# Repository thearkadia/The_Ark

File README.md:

# The Ark - ¿Democracy's Favorite Device?

The Ark is a portable computer that can be upgraded, modded, or repaired by the user since it uses open-source software, the pcb files are available, and the parts can be purchased individually. It is powered by the [Raspberry Pi Compute Module](https://www.raspberrypi.org/products/compute-module-3-plus-lite/), and runs a modified version of Debian.

# Simplifying Democracy
One of the goals of the Ark is to simplify the process of participating in a democracy for citizens, journalists, and politicians in a safe and transparent way. To simplify participating in a Democracy we will develop open source applications that focus on different key aspects of a Democracy. 

(images below are only mockups of the applications. all companies, charities, and names are used for demonstration purposes only) 

* An open source application that allows citizens to keep track of the voting history of their representatives. 

# Simplifying Budgets, Boycotts, and Taxes

* An application for journalists and charities to easily recieve reccuring donations from supporters. 

* An application to simplify the process of boycotting companies by displaying what products and companies a conglomerate owns or has a stake in. With a search feature to find alternatives to the product\service they are looking to purchase. 

 <p align="center">
  <a href="mailto:nixoye@protonmail.com"></center>
Email Us</a> </p>

<p align="center"> <a href="https://www.crowdsupply.com/the-arkadia/the-ark-dev-kit"> Crowdsupply Campaign </center> </p></a>
<p>
 <p align="center">
  Follow us on <a href="https://instagram.com/thearkadia">Instagram </a> or <a href="http://www.twitter.com/nixoye">Twitter</a></p>
    
<p align="center">  It has to start somewhere. It has to start sometime.
      </center> 
 </p>

<p align="center"> What better place than here? What better time than now? </center>

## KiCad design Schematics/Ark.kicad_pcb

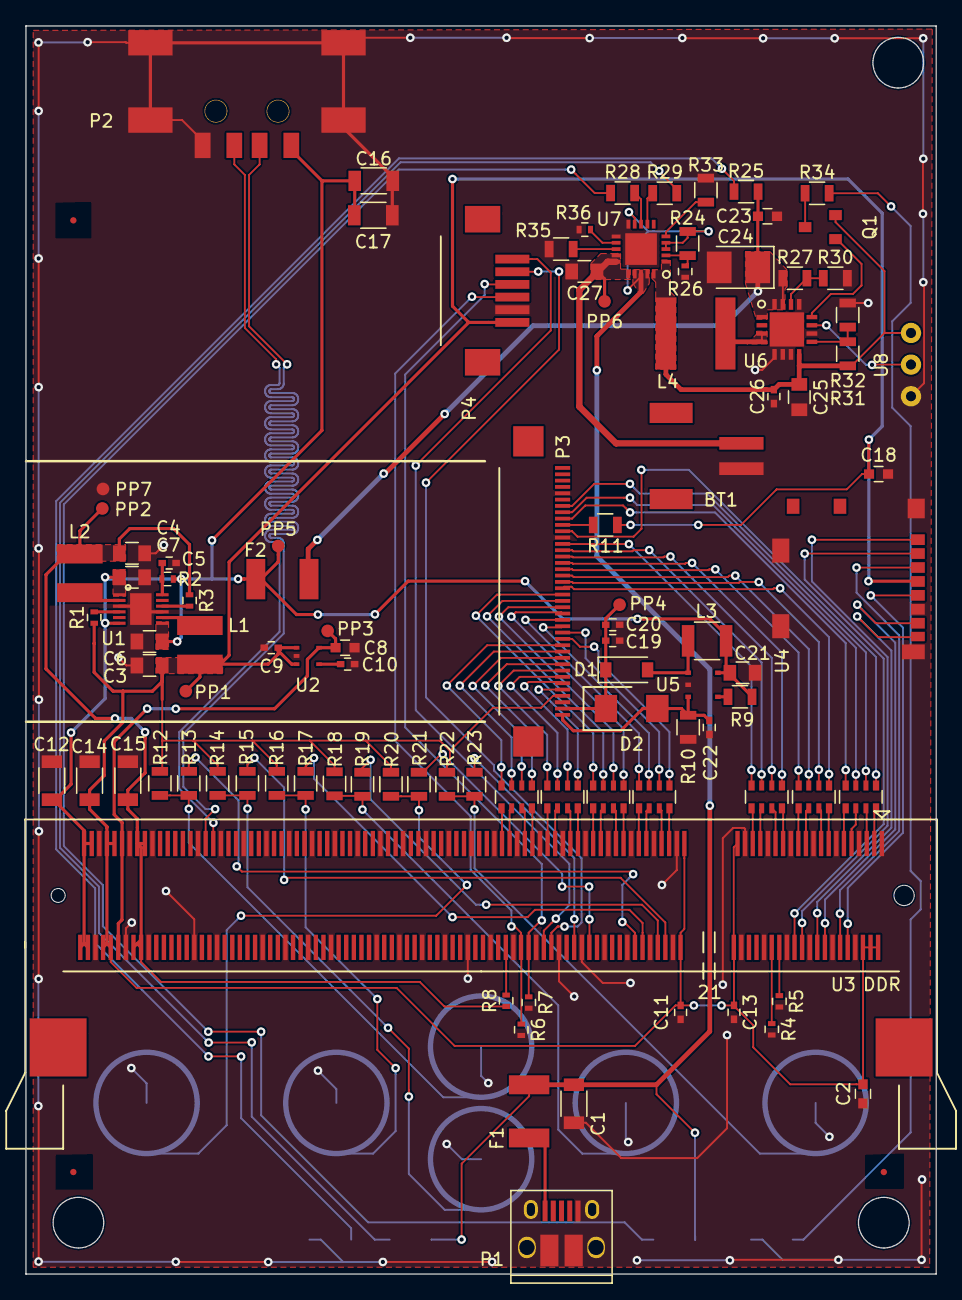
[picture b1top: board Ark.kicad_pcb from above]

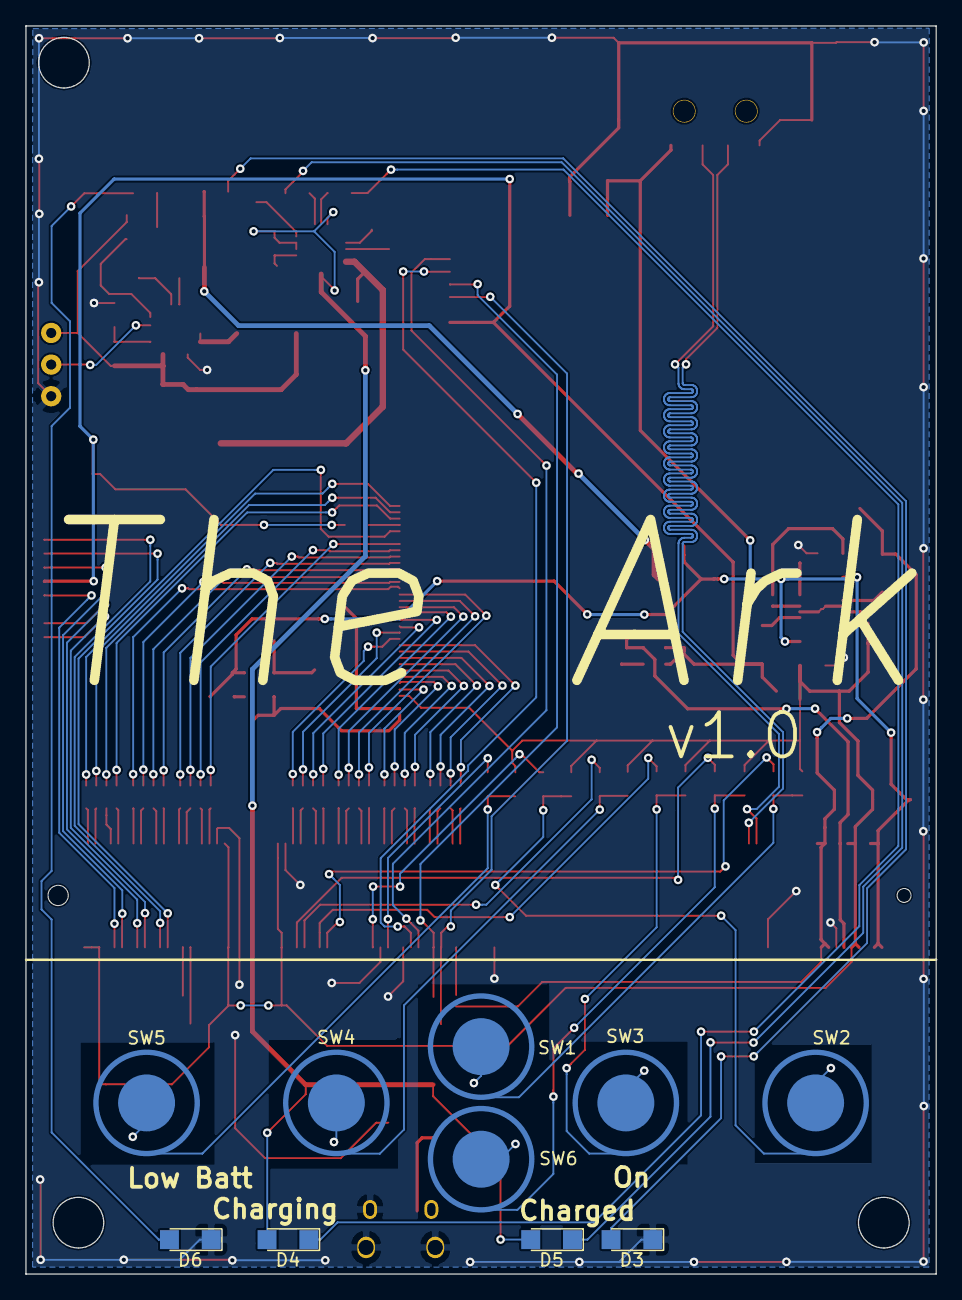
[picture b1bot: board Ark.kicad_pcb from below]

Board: 2 copper layers, 71.9 x 98.6 mm, 112 parts (10 on the bottom side), 120 nets.

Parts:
BT1: JST 2-PH; JST_2_PH
C1, C12, C14, C15, C16, C17: 47uF; C_1206
C2, C8, C18: 4.7uF; C_0603
C3, C4, C6, C7, C21, C25, C27: 10uF; C_0805
C5, C10, C22, C26: 100nF; C_0402
C9, C11, C13, C19, C20: 1uF; C_0402
C23: 2.2uF; C_0603
C24: 100uF; CP_Tantalum_Case-B_EIA-3528-21_Reflow
D1: MBR0540; D_SOD-123
D2: SMAZ24-TP
D3: Blue; LED_1206
D4: Orange; LED_1206
D5: Green; LED_1206
D6: Red; LED_1206
F1, F2: MF-MSMF200
L1, L2: 4.7uH; SRN4018-4R7M
L3: BRL3225T150K; C_1210
L4: 6.8uH; ASPI-0615FS-6R8M-T2
P1: USB_OTG; USB_Micro-B_10103594-0001LF
P2: USB_A; Wurth_USB_732-11179-1-ND
P3: 40_Pin_LCD_Out; LCD_Molex_Connector
P4: 6_Pin_Touch_In; Touch_Molex_Connector
P5, P6, P7: CONN_01X01; Fiducial
PP1, PP2, PP3, PP4, PP5, PP6, PP7: Test_Point
Q1: MMUN2133LT1G
R1, R3: 0R; R_0402
R2, R4, R5, R6, R7, R8, R26, R36: 100k; R_0402
R9, R11, R12, R14, R16, R18, R20, R22: 10k; R_0805
R10: 12; R_0805
R13, R15, R17, R19, R21, R23, R25, R28, R29, R34, R35: 1k; R_0805
R24: 270k; R_0805
R27, R31: 1.87M; R_0805
R30: 200k; R_0805
R32: 340k; R_0805
R33: 15k; R_0805
RP1, RP2, RP3, RP4, RP5, RP6, RP7: 33 R_PACK4; R_Array_Convex_4x0603
SW1, SW2, SW3, SW4, SW5, SW6: SW_PUSH_SMALL_H; Snapdome_SW
U1: PAM2306AYPKE
U2: AP7115-25SEG; AP7115-25SEG-7
U3: DDR2_SODIMM_CM_3_Lite; Socket_SODIMM_DDR2
U4: 1040310811; uSD_1040310811
U5: FAN5333BSX
U6: TPS61090RSAR
U7: MCP73871
U8: SPDT_switch; spdt_switch_MHSS1105

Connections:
1V8: C4.1, C15.1, L2.2, PP2.1, R3.1, R8.2, U3.183, U3.184, U3.185, U3.186
3V3: C2.1, C3.1, C9.1, C11.1, C13.1, C14.1, C18.1, L1.2, P3.4, P4.1, PP1.1, R1.1, R11.1, R12.2, R14.2, R16.2, R18.2, R20.2, R22.2, U2.1, U2.3, U3.2, U3.4, U3.6, U3.39, U3.40, U3.41, U3.42, U3.191, U3.192, U3.193, U3.194, U4.4
5V: C6.1, C7.1, C12.1, C16.1, C17.1, C21.1, F2.1, L3.1, P2.1, PP5.1, R2.1, R9.2, U1.1, U1.6, U1.7, U3.197, U3.198, U3.199, U3.200, U5.5
24V: C19.2, C20.2, D1.1, D2.1, P3.2, PP4.1
A: R21.2, U3.66
A_IN: R20.1, R21.1, SW2.1
B: R23.2, U3.70
B0: RP5.8, U3.15
B1: RP5.7, U3.17
B2: RP5.6, U3.21
B3: RP5.5, U3.23
B4: RP6.8, U3.27
B5: RP6.7, U3.29
B6: RP6.6, U3.33
B7: RP6.5, U3.35
B_IN: R22.1, R23.1, SW5.1
CM_VDAC: C8.1, PP3.1, U2.5, U3.189, U3.190
DE: RP7.7, U3.5
DOWN: R15.2, U3.46
DOWN_IN: R14.1, R15.1, SW6.1
EN_PWR: U6.11, U8.2
G0: RP3.8, U3.45
G1: RP3.7, U3.47
G2: RP3.6, U3.51
G3: RP3.5, U3.53
G4: RP4.8, U3.57
G5: RP4.7, U3.59
G6: RP4.6, U3.63
G7: RP4.5, U3.65
GND: BT1.2, C1.2, C2.2, C3.2, C4.2, C5.2, C6.2, C7.2, C8.2, C9.2, C10.2, C11.2, C12.2, C13.2, C14.2, C15.2, C16.2, C17.2, C18.2, C19.1, C20.1, C21.2, C22.2, C23.2, C24.2, C25.2, C26.2, C27.2, D3.1, D6.1, P1.5, P1.6, P2.4, P2.5, P3.3, P3.29, P3.36, P4.2, PP7.1, R4.2, R5.2, R6.2, R7.2, R10.1, R26.2, R30.2, R32.2, R33.2, R35.2, R36.2, SW1.2, SW2.2, SW3.2, SW4.2, SW5.2, SW6.2, U1.3, U1.9, U1.13, U2.2, U3.1, U3.7, U3.8, U3.13, U3.14, U3.19, U3.20, U3.25, U3.26, U3.31, U3.32, U3.37, U3.38, U3.43, U3.44, U3.49, U3.50, U3.55, U3.56, U3.61, U3.62, U3.67, U3.68, U3.73, U3.74, U3.79, U3.80, U3.85, U3.86, U3.91, U3.92, U3.97, U3.98, U3.103, U3.104, U3.109, U3.110, U3.115, U3.116, U3.121, U3.122, U3.127, U3.133, U3.134, U3.139, U3.140, U3.145, U3.146, U3.151, U3.152, U3.157, U3.163, U3.164, U3.169, U3.170, U3.181, U3.182, U3.187, U3.188, U3.195, U3.196, U4.6, U4.11, U4.12, U4.13, U4.14, U5.2, U6.5, U6.6, U6.7, U6.10, U6.13, U6.17, U7.10, U7.11, U7.21, U8.1
HSYNC: RP7.5, U3.11
INT: P4.5, U3.76
LEDK: C22.1, D2.2, P3.1, R10.2, U5.3
LEFT: R17.2, U3.52
LEFT_IN: R16.1, R17.1, SW3.1
unnamed: BT1.1, C27.1, PP6.1, U7.14, U7.15, U7.16
unnamed: C5.1, R2.2, U1.12
unnamed: C10.1, U2.4
unnamed: C23.1, C24.1, F2.2, R25.1, R27.1, U6.1, U6.15, U6.16
unnamed: D1.2, L3.2, U5.1
unnamed: D3.2, R25.2
unnamed: D4.1, R28.1
unnamed: D5.1, R29.1
unnamed: D6.2, R34.2
unnamed: F1.2, P1.1
unnamed: L1.1, U1.8
unnamed: L2.1, U1.2
unnamed: L4.2, U6.3, U6.4
unnamed: P3.5, RP1.1
unnamed: P3.6, RP1.2
unnamed: P3.7, RP1.3
unnamed: P3.8, RP1.4
unnamed: P3.9, RP2.1
unnamed: P3.10, RP2.2
unnamed: P3.11, RP2.3
unnamed: P3.12, RP2.4
unnamed: P3.13, RP3.1
unnamed: P3.14, RP3.2
unnamed: P3.15, RP3.3
unnamed: P3.16, RP3.4
unnamed: P3.17, RP4.1
unnamed: P3.18, RP4.2
unnamed: P3.19, RP4.3
unnamed: P3.20, RP4.4
unnamed: P3.21, RP5.1
unnamed: P3.22, RP5.2
unnamed: P3.23, RP5.3
unnamed: P3.24, RP5.4
unnamed: P3.25, RP6.1
unnamed: P3.26, RP6.2
unnamed: P3.27, RP6.3
unnamed: P3.28, RP6.4
unnamed: P3.30, RP7.1
unnamed: P3.31, R11.2
unnamed: P3.32, RP7.4
unnamed: P3.33, RP7.3
unnamed: P3.34, RP7.2
unnamed: Q1.1, U6.12
unnamed: Q1.3, R34.1
unnamed: R1.2, U1.4
unnamed: R3.2, U1.10
unnamed: R4.1, U3.30
unnamed: R5.1, U3.28
unnamed: R8.1, U3.88
unnamed: R9.1, U5.4
unnamed: R24.2, R26.1, U7.2
unnamed: R27.2, R30.1, U6.14
unnamed: R28.2, U7.8
unnamed: R29.2, U7.7
unnamed: R31.2, R32.1, U6.9
unnamed: R33.1, U7.5
unnamed: R35.1, U7.13
unnamed: R36.1, U7.12
ODCK: RP7.8, U3.3
PWR_IN: C1.1, D4.2, D5.2, F1.1, R24.1, U7.3, U7.4, U7.9, U7.17, U7.18, U7.19
R0: RP1.8, U3.69
R1: RP1.7, U3.71
R2: RP1.6, U3.75
R3: RP1.5, U3.77
R4: RP2.8, U3.81
R5: RP2.7, U3.83
R6: RP2.6, U3.87
R7: RP2.5, U3.89
RESET: P4.6, U3.78
RIGHT: R19.2, U3.48
RIGHT_IN: R18.1, R19.1, SW4.1
SCL: P4.3, R6.1, U3.84
SDA: P4.4, R7.1, U3.82
SDX_CLK: U3.10, U4.5
SDX_CMD: U3.12, U4.3
SDX_D0: U3.16, U4.7
SDX_D1: U3.18, U4.8
SDX_D2: U3.22, U4.1
SDX_D3: U3.24, U4.2
UP: R13.2, U3.54
UP_IN: R12.1, R13.1, SW1.1
USB_D+: P2.3, U3.165
USB_D-: P2.2, U3.167
VBAT: C25.1, C26.1, L4.1, Q1.2, R31.1, U6.8, U7.1, U7.20, U8.3
VSYNC: RP7.6, U3.9

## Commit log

2018-04-03 Create i
2018-04-03 cleaning up the repo
2018-04-03 morecleaning
2018-04-03 cleaningcomplete
2018-04-03 folder
2018-04-03 folder
    added files to folder so repo is cleaner
2018-04-03 folder
    added files to folders so the repo is cleaner
2018-04-03 Bills Of Materials
2018-04-04 3D printable case
2018-04-04 files to boot up
2018-04-04 instructions to boot up
2018-04-04 MIT LIcense
2018-04-04 screenshots of pcb design
2018-04-04 test
2018-04-04 2.3.18
2018-04-06 Set theme jekyll-theme-minimal
2018-04-06 Set theme jekyll-theme-time-machine
2018-04-06 Set theme jekyll-theme-merlot
2018-04-06 Set theme jekyll-theme-slate
2018-04-06 Set theme jekyll-theme-cayman
2018-04-06 Set theme jekyll-theme-leap-day
2018-04-06 Set theme jekyll-theme-modernist
2018-04-06 Set theme jekyll-theme-hacker
2018-04-06 Set theme jekyll-theme-architect
2018-04-06 Set theme jekyll-theme-midnight
2018-04-06 Set theme jekyll-theme-tactile
2018-04-06 Set theme jekyll-theme-dinky
2018-04-06 images
2018-04-09 vicpic
2018-05-02 sketches
2018-05-02 mockups
2018-05-21 files
2019-02-04 2019
2019-03-03 pngs
2019-03-03 anim
2019-03-22 Design-Assets
2019-03-26 blender file
2019-03-27 .blend
2019-07-01 photo
2019-07-01 tmtr's license
2019-07-02 case-snapclose
2019-09-17 ark-heart
